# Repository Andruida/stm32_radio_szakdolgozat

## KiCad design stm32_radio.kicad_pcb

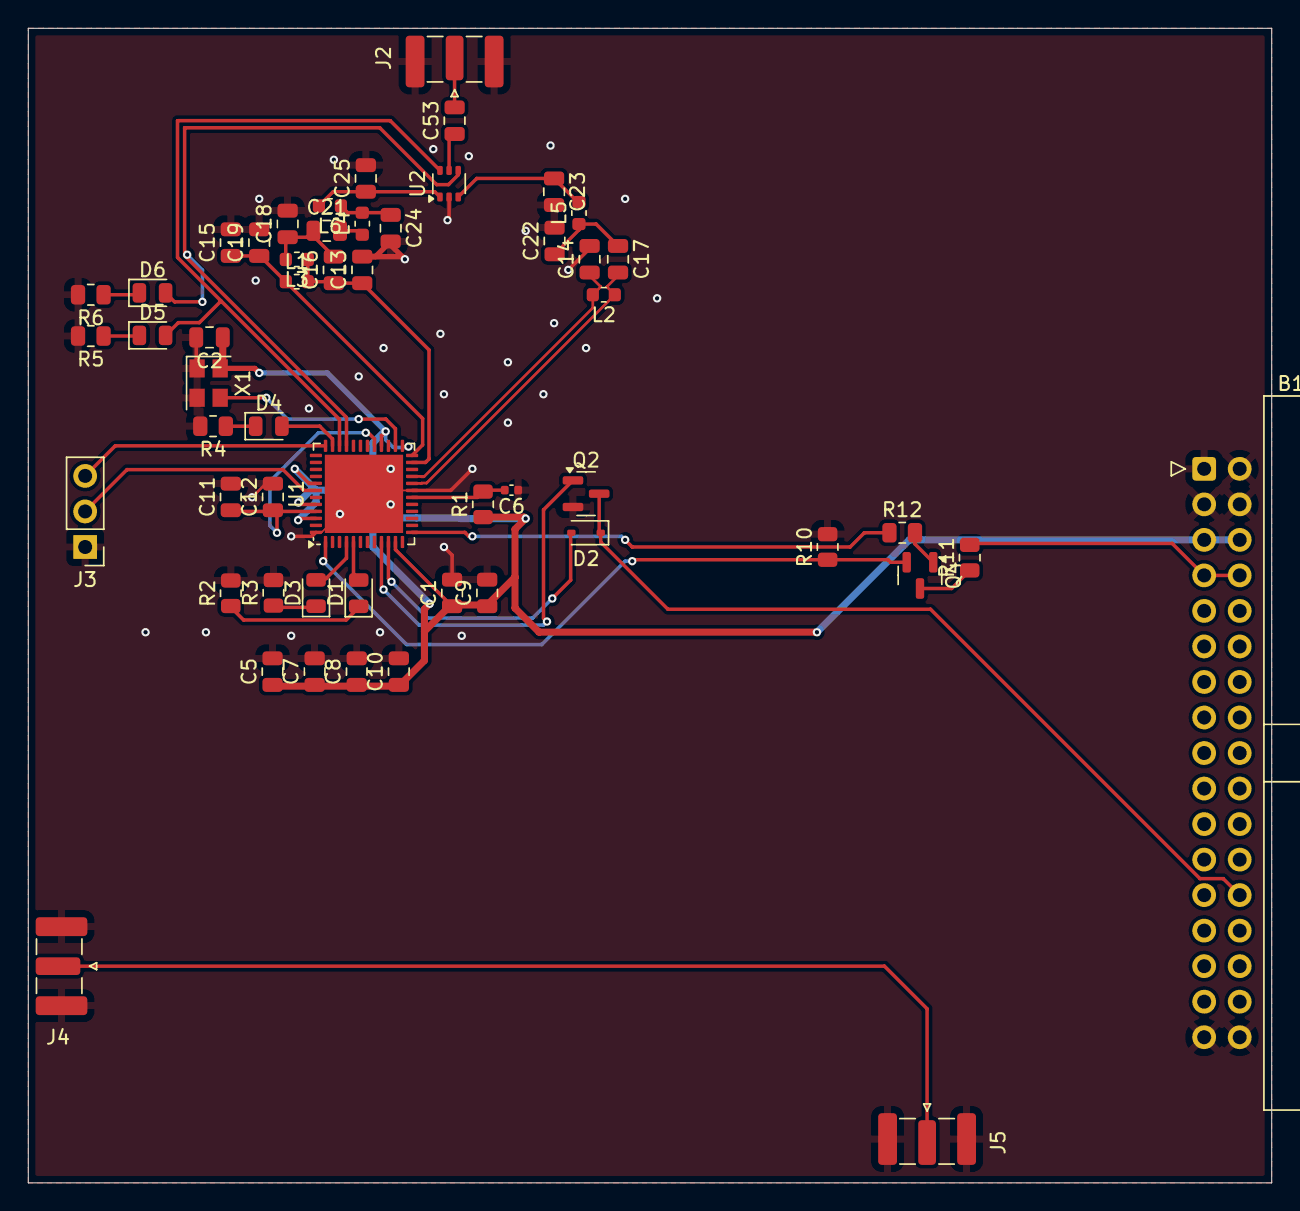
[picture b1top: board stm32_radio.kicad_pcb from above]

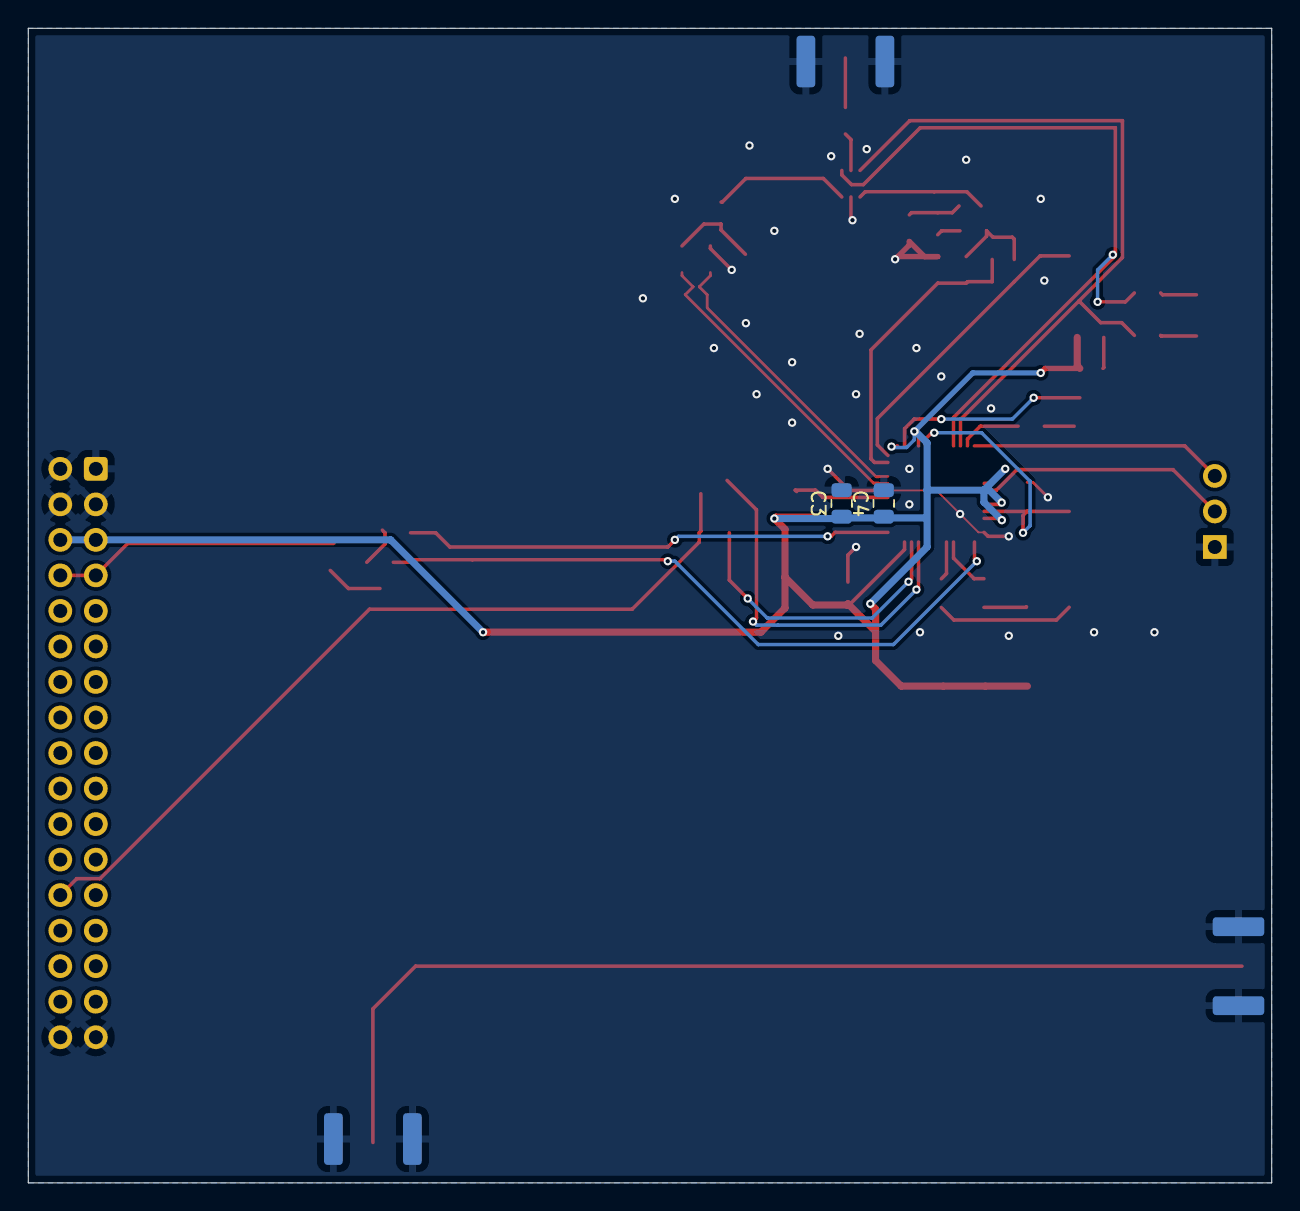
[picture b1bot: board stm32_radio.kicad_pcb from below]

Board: 2 copper layers, 88.9 x 82.5 mm, 56 parts (2 on the bottom side), 38 nets.

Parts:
B1: IDC-Header_2x17_P2.54mm_Horizontal
C1, C7, C8, C9: 470n; C_0805_2012Metric
C2: 12p; C_0805_2012Metric
C3: 100n; C_0805_2012Metric
C4: 1u; C_0805_2012Metric
C5, C10: 4u7; C_0805_2012Metric
C6: 1n; C_0402_1005Metric
C11, C12: 10n; C_0805_2012Metric
C13: 0p7; C_0805_2012Metric
C14: 4.7pF; C_0805_2012Metric
C15, C21, C53: 68p; C_0805_2012Metric
C16: 2.7p; C_0805_2012Metric
C17: 3.6pF; C_0805_2012Metric
C18: 15p; C_0805_2012Metric
C19: 47n; C_0805_2012Metric
C22, C23: 6.8pF; C_0805_2012Metric
C24: 8p2; C_0805_2012Metric
C25: 3.3p; C_0805_2012Metric
D1, D3, D4, D5, D6: Green; LED_0805_2012Metric
D2: D_Schottky; D_SOD-323
J2, J4, J5: Conn_Coaxial_Small; SMA_Samtec_SMA-J-P-H-ST-EM1_EdgeMount
J3: Conn_01x03_Pin; PinHeader_1x03_P2.54mm_Vertical
L1: 56n; L_0603_1608Metric
L2, L5: 33nH; L_0603_1608Metric
L3: 11n; L_0603_1608Metric
L4: 22n; L_0603_1608Metric
L6: 0; L_0603_1608Metric
Q2: DMN1019USN-7; SOT-23
Q4: Q_NPN; SOT-23
R1, R10: 10k; R_0805_2012Metric
R2, R3, R4, R5, R6: 470; R_0805_2012Metric
R11: 20k; R_0805_2012Metric
R12: 100k; R_0805_2012Metric
U1: STM32WL55CCU7; QFN-48-1EP_7x7mm_P0.5mm_EP5.6x5.6mm
U2: AS179-92LF; SOT-363_SC-70-6
X1: 32MHz; Oscillator_SMD_Abracon_ASE-4Pin_3.2x2.5mm

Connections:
/50_ohm_test: J4.1 (In), J5.1 (In)
/Radio MCU/1V5: C11.1, C12.1, U1.29 (VDDRF1V55), U1.45 (VFBSMPS)
/Radio MCU/3V3: B1.5 (Reg_bus_3v3), B1.6 (Reg_bus_3v3), C1.1, C2.1, C3.1, C4.1, C5.1, C7.1, C8.1, C9.1, C10.1, R1.1, U1.11 (VDD), U1.25 (VDDPA), U1.28 (VDDRF), U1.41 (VDDA), U1.44 (VDD), U1.46 (VDDSMPS), X1.4 (Vdd)
/Radio MCU/RF out: C53.2, J2.1 (In)
/Radio MCU/RF out/50ohm_1: C16.2, C18.1, C21.1, L3.2
/Radio MCU/RF out/50ohm_2: C21.2, L4.1
/Radio MCU/RF out/50ohm_3: C24.1, L4.2, L6.1
/Radio MCU/RF out/50ohm_RX_1: C17.1, C22.1, L5.1
/Radio MCU/RF out/RFI_N: C14.1, L2.2, U1.21 (RFI_N)
/Radio MCU/RF out/RFI_P: C17.2, L2.1, U1.20 (RFI_P)
/Radio MCU/RF out/RFO_HP: C13.1, C16.1, L1.2, L3.1, U1.23 (RFO_HP)
/Radio MCU/RF out/RF_RX: C23.1, L5.2, U2.3 (J2)
/Radio MCU/RF out/RF_TX: C25.1, L6.2, U2.1 (J3)
/Radio MCU/RF out/RF_unfiltered: C53.1, U2.5 (J1)
/Radio MCU/RF out/RX_EN: D5.2 (A), U1.34 (PA11), U2.6 (V2)
/Radio MCU/RF out/TX_EN: D6.2 (A), U1.33 (PA10), U2.4 (V1)
/Radio MCU/RF out/VR_PA: C15.1, C19.1, L1.1, U1.24 (VR_PA)
/Radio MCU/SWCLK: J3.2, U1.42 (PA14)
/Radio MCU/SWDIO: J3.3, U1.36 (PA13)
/Radio MCU/UART: B1.26 (COM_Data), D2.1 (K), Q2.3 (D)
/Radio MCU/UART2_RX: D2.2 (A), U1.10 (PA3)
/Radio MCU/UART2_TX: Q2.1 (G), U1.9 (PA2)
/Radio MCU/VBAT: B1.7 (Unreg_bus), B1.8 (Unreg_bus), R11.2
GND: B1.1 (GND), B1.2 (GND), B1.3 (GND), B1.4 (GND), B1.33 (GND), B1.34 (GND), C1.2, C2.2, C3.2, C4.2, C5.2, C6.1, C7.2, C8.2, C9.2, C10.2, C11.2, C12.2, C13.2, C14.2, C15.2, C18.2, C19.2, C22.2, C23.2, C24.2, C25.2, J2.2 (Ext), J3.1, J4.2 (Ext), J5.2 (Ext), Q2.2 (S), R2.2, R3.2, R4.2, R5.2, R6.2, R10.2, U1.19 (PH3), U1.48 (VSSSMPS), U1.49 (VSS), U2.2 (GND), X1.1 (EN), X1.2 (GND)
unnamed: D1.2 (A), U1.5 (PB7)
unnamed: D1.1 (K), R2.1
unnamed: D3.2 (A), U1.4 (PB6)
unnamed: D3.1 (K), R3.1
unnamed: D4.2 (A), U1.35 (PA12)
unnamed: D4.1 (K), R4.1
unnamed: D5.1 (K), R5.1
unnamed: D6.1 (K), R6.1
unnamed: Q4.1 (B), R12.2
unnamed: Q4.3 (C), R11.1
unnamed: Q4.2 (E), R10.1, U1.1 (PB3)
unnamed: C6.2, R1.2, U1.18 (NRST)
unnamed: U1.26 (OSC_IN), X1.3 (OUT)
unnamed: R12.1, U1.13 (PA5)

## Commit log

2025-10-06 Almost ready for production
2025-10-06 Fix footprints
2025-10-06 Finalize design
2025-10-06 Fabrication files
2025-10-06 Altered LCSC part numbers according to current stock
2025-10-06 Changed crystal to oscillator
2025-10-06 Added a pair of SMA connectors for measurement
